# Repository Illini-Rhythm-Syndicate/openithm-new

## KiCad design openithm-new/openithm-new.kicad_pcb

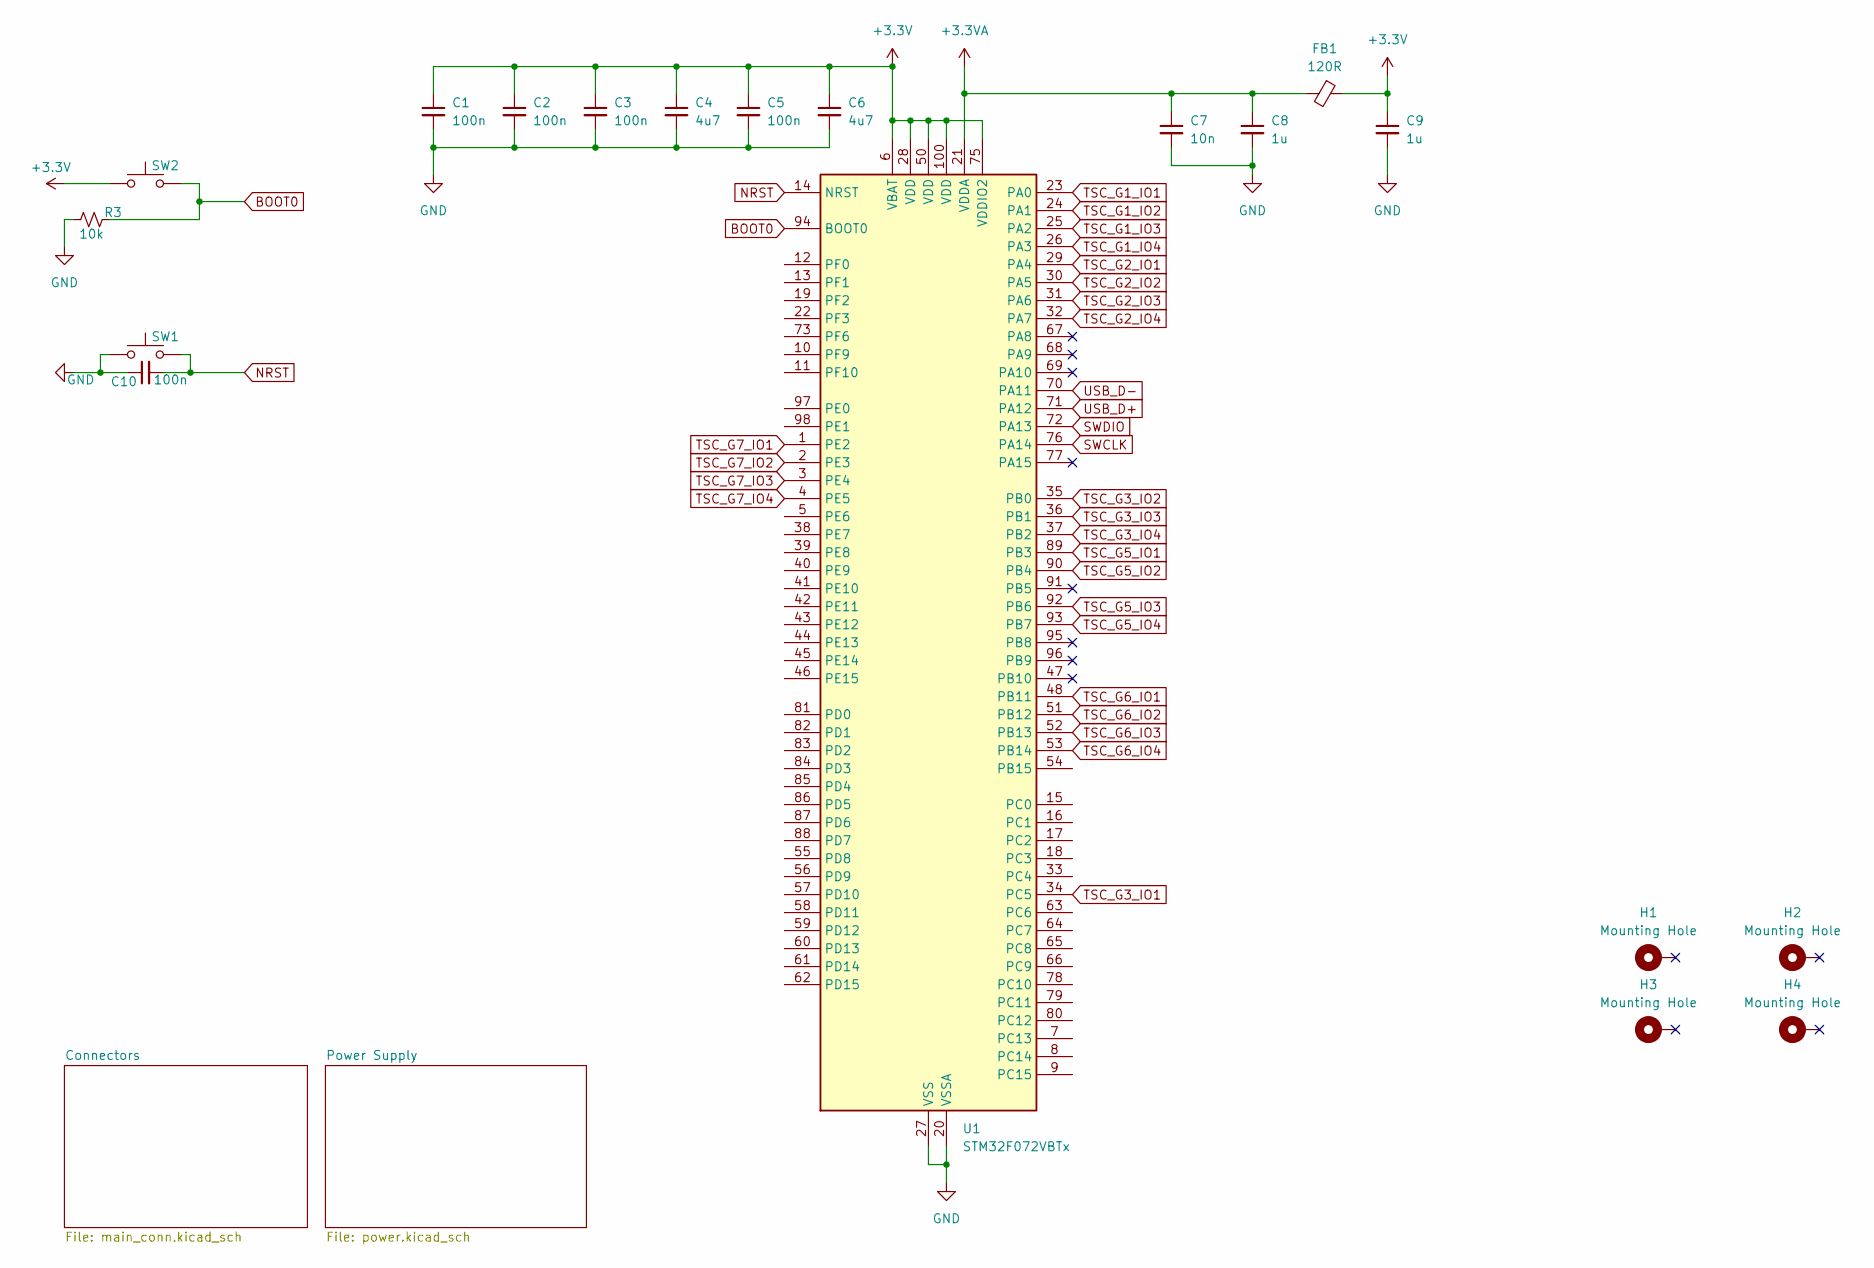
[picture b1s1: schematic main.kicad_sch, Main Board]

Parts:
C1, C2, C3, C5, C10: 100n; C_0402_1005Metric
C4, C6: 4u7; C_0603_1608Metric
C7: 10n; C_0402_1005Metric
C8, C9: 1u; C_0603_1608Metric
FB1: 120R; L_0603_1608Metric
H1, H2, H3, H4: Mounting Hole; MountingHole_2.2mm_M2_Pad
R3: 10k; R_0402_1005Metric
SW1, SW2: SW_Push; SW_Tactile_SPST_NO_Straight_CK_PTS636Sx25SMTRLFS
U1: STM32F072VBTx; LQFP-100_14x14mm_P0.5mm

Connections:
+3.3V: C1.1, C2.1, C3.1, C4.1, C5.1, C6.1, C9.1, FB1.1, SW2.1, U1.6 (VBAT), U1.28 (VDD), U1.50 (VDD), U1.75 (VDDIO2), U1.100 (VDD); also elsewhere on the board
+3.3VA: C7.1, C8.1, FB1.2, U1.21 (VDDA)
BOOT0: R3.2, SW2.2, U1.94 (BOOT0)
GND: C1.2, C2.2, C3.2, C4.2, C5.2, C6.2, C7.2, C8.2, C9.2, C10.1, R3.1, SW1.1, U1.20 (VSSA), U1.27 (VSS), U1.49 (VSS), U1.74 (VSS), U1.99 (VSS); also elsewhere on the board
NRST: C10.2, SW1.2, U1.14 (NRST)
SWCLK: U1.76 (PA14); also elsewhere on the board
SWDIO: U1.72 (PA13); also elsewhere on the board
TSC_G1_IO1: U1.23 (PA0); also elsewhere on the board
TSC_G1_IO2: U1.24 (PA1); also elsewhere on the board
TSC_G1_IO3: U1.25 (PA2); also elsewhere on the board
TSC_G1_IO4: U1.26 (PA3); also elsewhere on the board
TSC_G2_IO1: U1.29 (PA4); also elsewhere on the board
TSC_G2_IO2: U1.30 (PA5); also elsewhere on the board
TSC_G2_IO3: U1.31 (PA6); also elsewhere on the board
TSC_G2_IO4: U1.32 (PA7); also elsewhere on the board
TSC_G3_IO1: U1.34 (PC5); also elsewhere on the board
TSC_G3_IO2: U1.35 (PB0); also elsewhere on the board
TSC_G3_IO3: U1.36 (PB1); also elsewhere on the board
TSC_G3_IO4: U1.37 (PB2); also elsewhere on the board
TSC_G5_IO1: U1.89 (PB3); also elsewhere on the board
TSC_G5_IO2: U1.90 (PB4); also elsewhere on the board
TSC_G5_IO3: U1.92 (PB6); also elsewhere on the board
TSC_G5_IO4: U1.93 (PB7)
TSC_G6_IO1: U1.48 (PB11); also elsewhere on the board
TSC_G6_IO2: U1.51 (PB12); also elsewhere on the board
TSC_G6_IO3: U1.52 (PB13); also elsewhere on the board
TSC_G6_IO4: U1.53 (PB14)
TSC_G7_IO1: U1.1 (PE2); also elsewhere on the board
TSC_G7_IO2: U1.2 (PE3); also elsewhere on the board
TSC_G7_IO3: U1.3 (PE4); also elsewhere on the board
TSC_G7_IO4: U1.4 (PE5); also elsewhere on the board
USB_D+: U1.71 (PA12); also elsewhere on the board
USB_D-: U1.70 (PA11); also elsewhere on the board

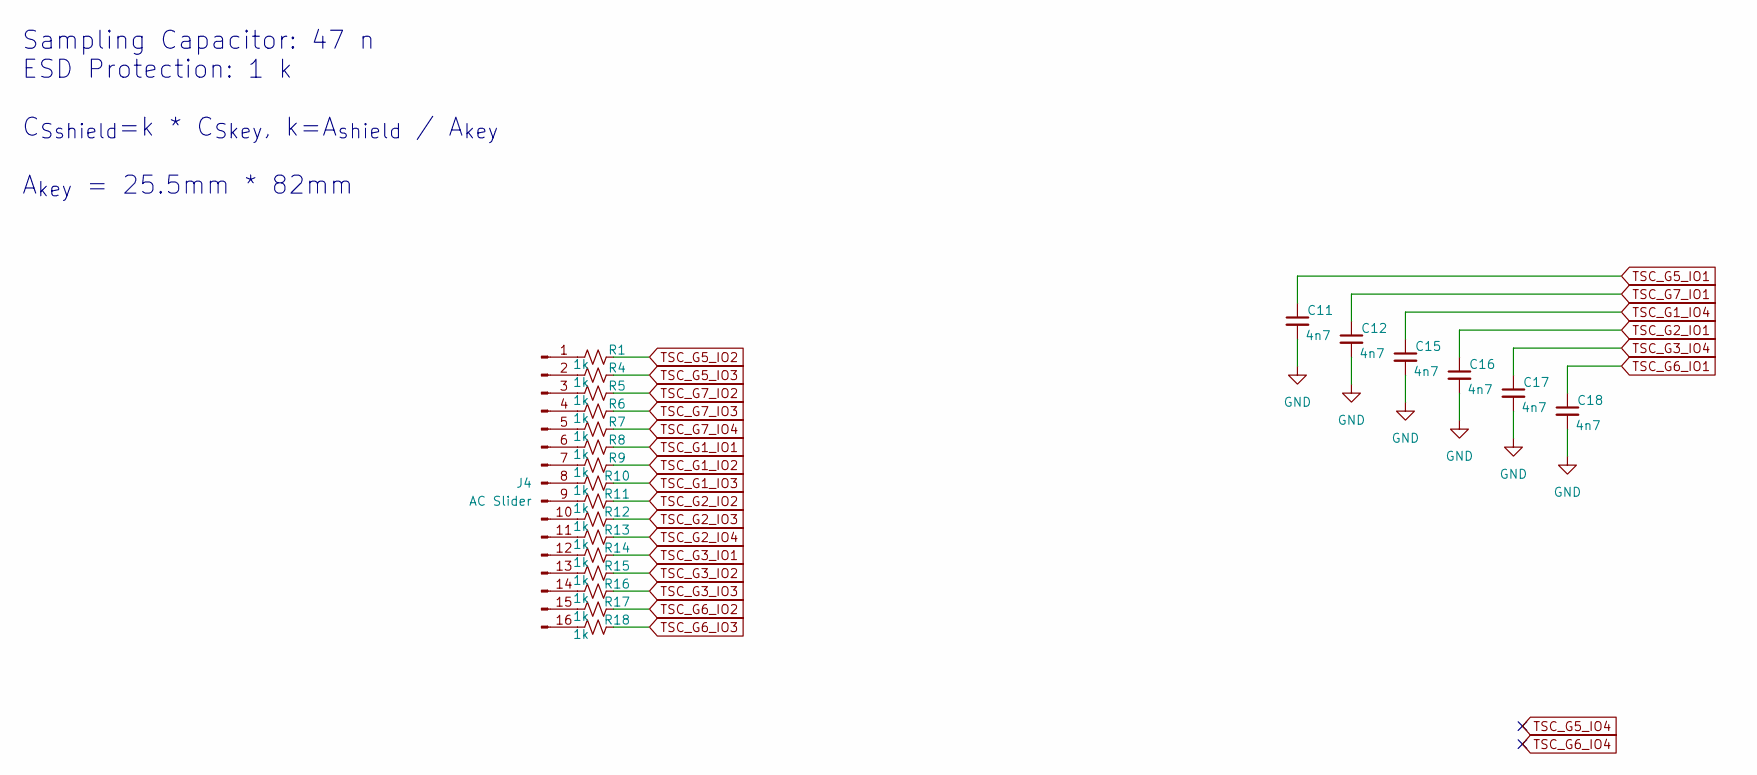
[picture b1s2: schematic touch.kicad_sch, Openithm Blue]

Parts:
C11, C12, C15, C16, C17, C18: 4n7; C_0402_1005Metric
J4: AC Slider; AC_SLIDER
R1, R4, R5, R6, R7, R8, R9, R10, R11, R12, R13, R14, R15, R16, R17, R18: 1k; R_0402_1005Metric

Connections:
GND: C11.2, C12.2, C15.2, C16.2, C17.2, C18.2; also elsewhere on the board
unnamed: J4.1, R1.1
unnamed: J4.2, R4.1
unnamed: J4.3, R5.1
unnamed: J4.4, R6.1
unnamed: J4.5, R7.1
unnamed: J4.6, R8.1
unnamed: J4.7, R9.1
unnamed: J4.8, R10.1
unnamed: J4.9, R11.1
unnamed: J4.10, R12.1
unnamed: J4.11, R13.1
unnamed: J4.12, R14.1
unnamed: J4.13, R15.1
unnamed: J4.14, R16.1
unnamed: J4.15, R17.1
unnamed: J4.16, R18.1
TSC_G1_IO1: R8.2; also elsewhere on the board
TSC_G1_IO2: R9.2; also elsewhere on the board
TSC_G1_IO3: R10.2; also elsewhere on the board
TSC_G1_IO4: C15.1; also elsewhere on the board
TSC_G2_IO1: C16.1; also elsewhere on the board
TSC_G2_IO2: R11.2; also elsewhere on the board
TSC_G2_IO3: R12.2; also elsewhere on the board
TSC_G2_IO4: R13.2; also elsewhere on the board
TSC_G3_IO1: R14.2; also elsewhere on the board
TSC_G3_IO2: R15.2; also elsewhere on the board
TSC_G3_IO3: R16.2; also elsewhere on the board
TSC_G3_IO4: C17.1; also elsewhere on the board
TSC_G5_IO1: C11.1; also elsewhere on the board
TSC_G5_IO2: R1.2; also elsewhere on the board
TSC_G5_IO3: R4.2; also elsewhere on the board
TSC_G6_IO1: C18.1; also elsewhere on the board
TSC_G6_IO2: R17.2; also elsewhere on the board
TSC_G6_IO3: R18.2; also elsewhere on the board
TSC_G7_IO1: C12.1; also elsewhere on the board
TSC_G7_IO2: R5.2; also elsewhere on the board
TSC_G7_IO3: R6.2; also elsewhere on the board
TSC_G7_IO4: R7.2; also elsewhere on the board

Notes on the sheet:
Sampling Capacitor: 47 n ESD Protection: 1 k C_{Sshield}=k * C_{Skey}, k=A_{shield} / A_{key} A_{key} = 25.5mm * 82mm

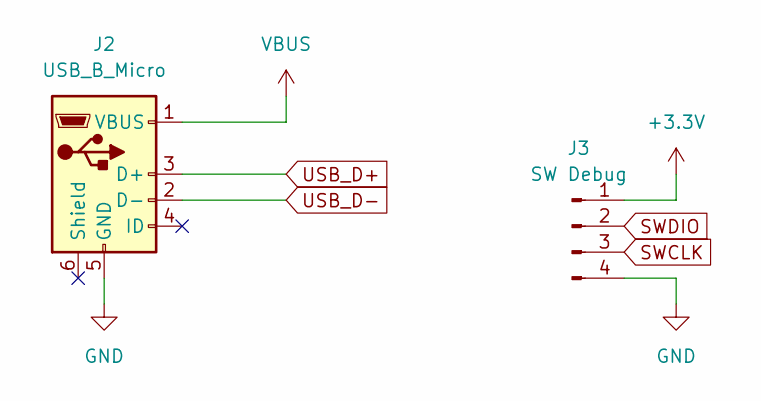
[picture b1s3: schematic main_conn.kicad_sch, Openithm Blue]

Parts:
J2: USB_B_Micro; USB_Micro-B_Wuerth_629105150521
J3: SW Debug; PinHeader_1x04_P2.54mm_Horizontal

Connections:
+3.3V: J3.1; also elsewhere on the board
GND: J2.5 (GND), J3.4; also elsewhere on the board
SWCLK: J3.3; also elsewhere on the board
SWDIO: J3.2; also elsewhere on the board
USB_D+: J2.3 (D+); also elsewhere on the board
USB_D-: J2.2 (D-); also elsewhere on the board
VBUS: J2.1 (VBUS); also elsewhere on the board

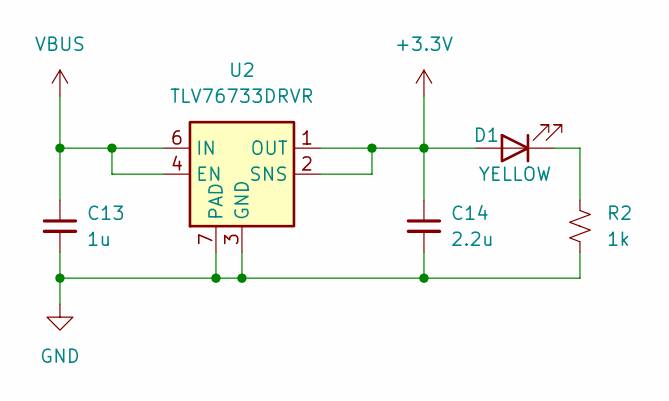
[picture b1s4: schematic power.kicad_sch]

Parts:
C13: 1u; C_0603_1608Metric
C14: 2.2u; C_0603_1608Metric
D1: YELLOW; LED_0603_1608Metric
R2: 1k; R_0402_1005Metric
U2: TLV76733DRVR; WSON-6-1EP_2x2mm_P0.65mm_EP1x1.6mm

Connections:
+3.3V: C14.1, D1.2 (A), U2.1 (OUT), U2.2 (SNS); also elsewhere on the board
GND: C13.2, C14.2, R2.2, U2.3 (GND), U2.5 (GND), U2.7 (PAD); also elsewhere on the board
unnamed: D1.1 (K), R2.1
VBUS: C13.1, U2.4 (EN), U2.6 (IN); also elsewhere on the board

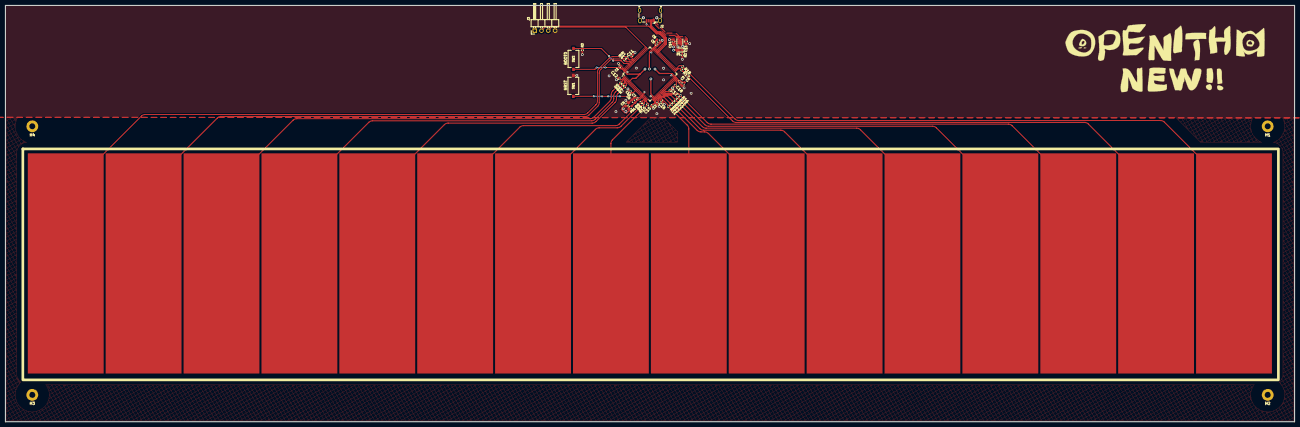
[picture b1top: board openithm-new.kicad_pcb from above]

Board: 2 copper layers, 480.0 x 155.0 mm, 49 parts (0 on the bottom side), 49 nets.

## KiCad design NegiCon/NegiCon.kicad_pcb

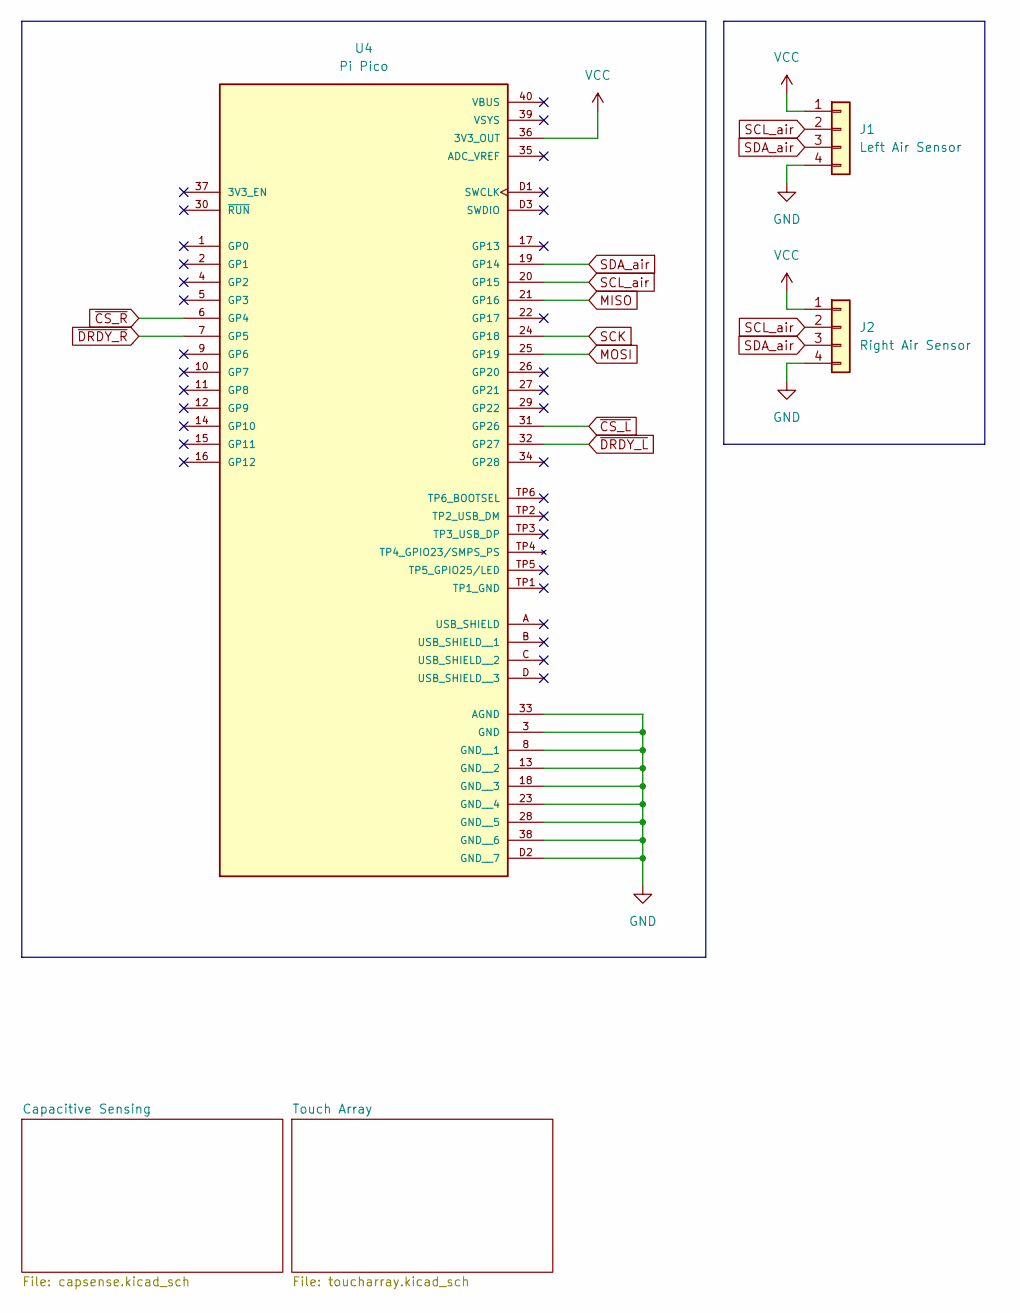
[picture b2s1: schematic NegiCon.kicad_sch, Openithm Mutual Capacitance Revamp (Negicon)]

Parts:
J1: Left Air Sensor; Molex_Nano-Fit_105313-xx04_1x04_P2.50mm_Horizontal
J2: Right Air Sensor; Molex_Nano-Fit_105313-xx04_1x04_P2.50mm_Horizontal
U4: Pi Pico; MODULE_SC0915; PARTREV 1.9

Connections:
GND: J1.4, J2.4, U4.3 (GND), U4.8 (GND__1), U4.13 (GND__2), U4.18 (GND__3), U4.23 (GND__4), U4.28 (GND__5), U4.33 (AGND), U4.38 (GND__6), U4.D2 (GND__7); also elsewhere on the board
MISO: U4.21 (GP16); also elsewhere on the board
MOSI: U4.25 (GP19); also elsewhere on the board
SCK: U4.24 (GP18); also elsewhere on the board
SCL_air: J1.2, J2.2, U4.20 (GP15)
SDA_air: J1.3, J2.3, U4.19 (GP14)
VCC: J1.1, J2.1, U4.36 (3V3_OUT); also elsewhere on the board
~CS_L: U4.31 (GP26); also elsewhere on the board
~CS_R: U4.6 (GP4); also elsewhere on the board
~DRDY_L: U4.32 (GP27); also elsewhere on the board
~DRDY_R: U4.7 (GP5); also elsewhere on the board

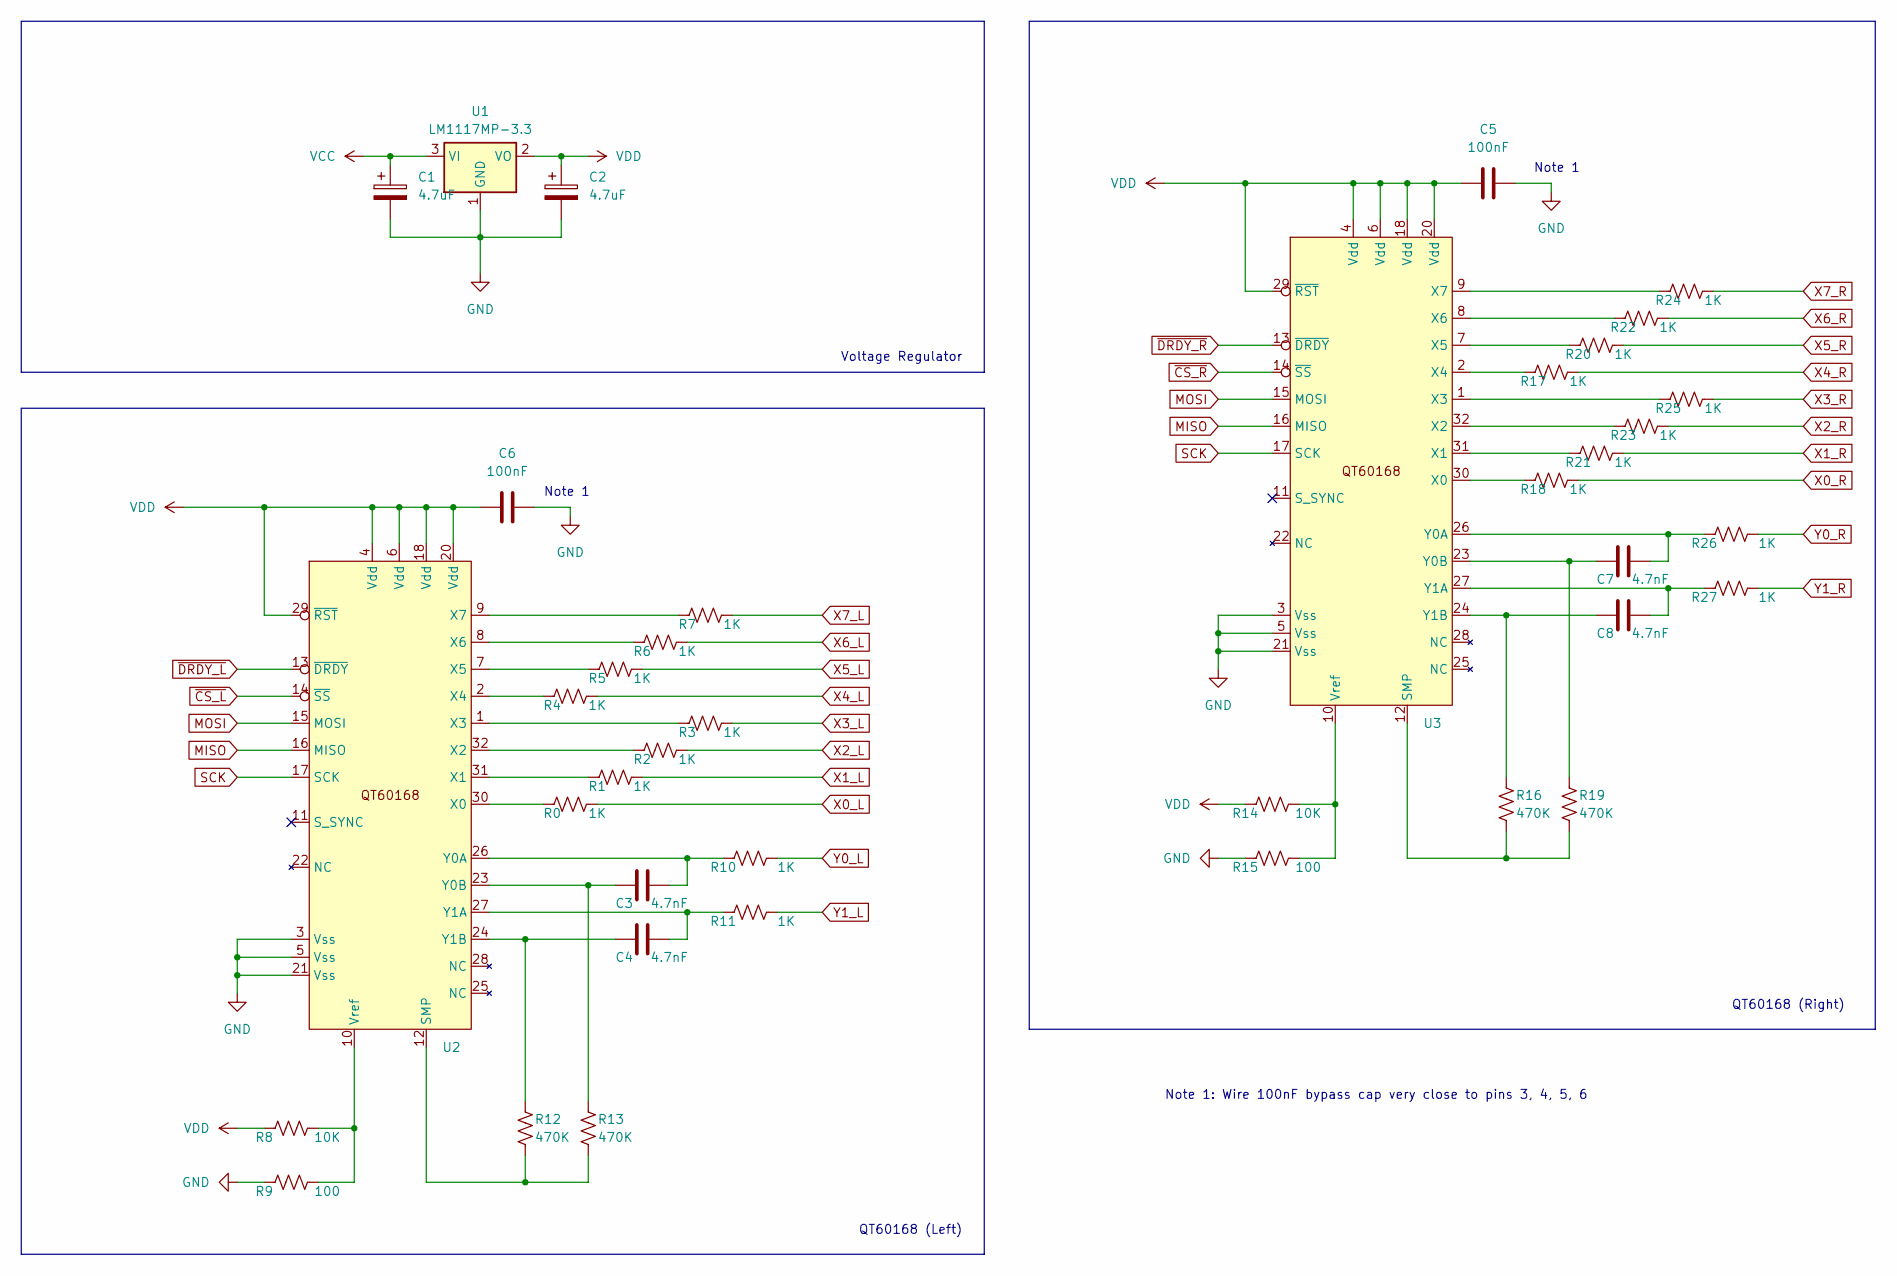
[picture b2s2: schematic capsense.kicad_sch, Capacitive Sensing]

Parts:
C1, C2: 4.7uF; C_0603_1608Metric
C3, C4, C7, C8: 4.7nF; C_0603_1608Metric
C5, C6: 100nF; C_0603_1608Metric
R0, R1, R2, R3, R4, R5, R6, R7, R10, R11, R17, R18, R20, R21, R22, R23, R24, R25, R26, R27: 1K; R_0603_1608Metric
R8, R14: 10K; R_0603_1608Metric
R9, R15: 100; R_0603_1608Metric
R12, R13, R16, R19: 470K; R_0603_1608Metric
U1: LM1117MP-3.3; SOT-223-3_TabPin2
U2, U3: TQFP-32_7x7mm_P0.8mm

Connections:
GND: C1.2, C2.2, C5.2, C6.2, R9.1, R15.1, U1.1 (GND), U2.3 (Vss), U2.5 (Vss), U2.21 (Vss), U3.3 (Vss), U3.5 (Vss), U3.21 (Vss); also elsewhere on the board
MISO: U2.16 (MISO), U3.16 (MISO); also elsewhere on the board
MOSI: U2.15 (MOSI), U3.15 (MOSI); also elsewhere on the board
unnamed: R12.2, R13.2, U2.12 (SMP)
unnamed: R8.1, R9.2, U2.10 (Vref)
unnamed: R0.1, U2.30 (X0)
unnamed: R1.1, U2.31 (X1)
unnamed: R2.1, U2.32 (X2)
unnamed: R3.1, U2.1 (X3)
unnamed: R4.1, U2.2 (X4)
unnamed: R5.1, U2.7 (X5)
unnamed: R6.1, U2.8 (X6)
unnamed: R7.1, U2.9 (X7)
unnamed: C3.2, R10.1, U2.26 (Y0A)
unnamed: C3.1, R13.1, U2.23 (Y0B)
unnamed: C4.2, R11.1, U2.27 (Y1A)
unnamed: C4.1, R12.1, U2.24 (Y1B)
unnamed: R16.2, R19.2, U3.12 (SMP)
unnamed: R14.1, R15.2, U3.10 (Vref)
unnamed: R18.1, U3.30 (X0)
unnamed: R21.1, U3.31 (X1)
unnamed: R23.1, U3.32 (X2)
unnamed: R25.1, U3.1 (X3)
unnamed: R17.1, U3.2 (X4)
unnamed: R20.1, U3.7 (X5)
unnamed: R22.1, U3.8 (X6)
unnamed: R24.1, U3.9 (X7)
unnamed: C7.2, R26.1, U3.26 (Y0A)
unnamed: C7.1, R19.1, U3.23 (Y0B)
unnamed: C8.2, R27.1, U3.27 (Y1A)
unnamed: C8.1, R16.1, U3.24 (Y1B)
SCK: U2.17 (SCK), U3.17 (SCK); also elsewhere on the board
VCC: C1.1, U1.3 (VI); also elsewhere on the board
VDD: C2.1, C5.1, C6.1, R8.2, R14.2, U1.2 (VO), U2.4 (Vdd), U2.6 (Vdd), U2.18 (Vdd), U2.20 (Vdd), U2.29 (~RST), U3.4 (Vdd), U3.6 (Vdd), U3.18 (Vdd), U3.20 (Vdd), U3.29 (~RST)
X0_L: R0.2; also elsewhere on the board
X0_R: R18.2; also elsewhere on the board
X1_L: R1.2; also elsewhere on the board
X1_R: R21.2; also elsewhere on the board
X2_L: R2.2; also elsewhere on the board
X2_R: R23.2; also elsewhere on the board
X3_L: R3.2; also elsewhere on the board
X3_R: R25.2; also elsewhere on the board
X4_L: R4.2; also elsewhere on the board
X4_R: R17.2; also elsewhere on the board
X5_L: R5.2; also elsewhere on the board
X5_R: R20.2; also elsewhere on the board
X6_L: R6.2; also elsewhere on the board
X6_R: R22.2; also elsewhere on the board
X7_L: R7.2; also elsewhere on the board
X7_R: R24.2; also elsewhere on the board
Y0_L: R10.2; also elsewhere on the board
Y0_R: R26.2; also elsewhere on the board
Y1_L: R11.2; also elsewhere on the board
Y1_R: R27.2; also elsewhere on the board
~CS_L: U2.14 (~SS); also elsewhere on the board
~CS_R: U3.14 (~SS); also elsewhere on the board
~DRDY_L: U2.13 (~DRDY); also elsewhere on the board
~DRDY_R: U3.13 (~DRDY); also elsewhere on the board

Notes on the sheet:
QT60168 (Right)
Voltage Regulator
QT60168 (Left)
Note 1
Note 1: Wire 100nF bypass cap very close to pins 3, 4, 5, 6

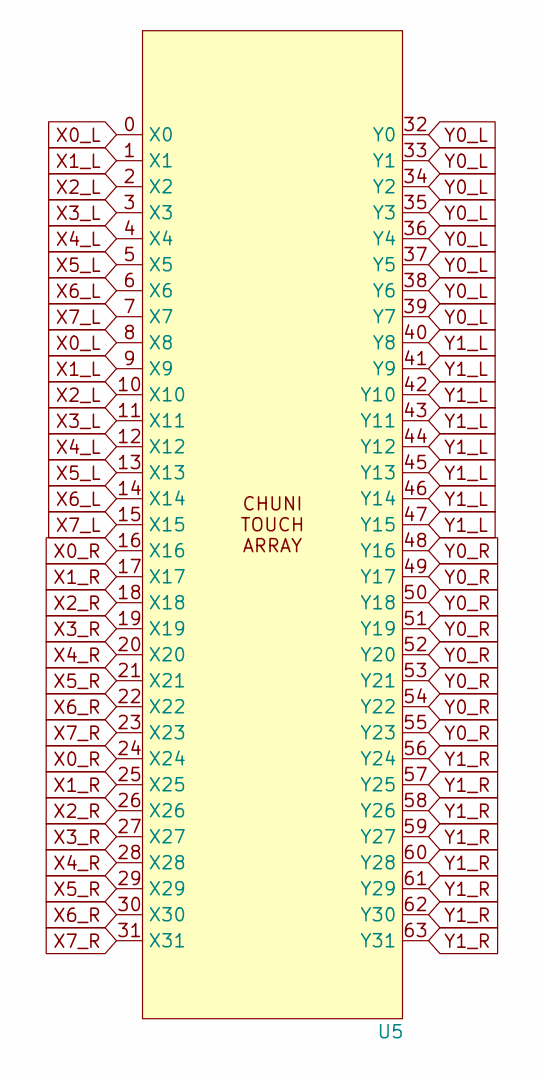
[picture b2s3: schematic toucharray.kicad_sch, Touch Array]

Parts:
U5: CH3MM64

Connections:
X0_L: U5.0 (X0), U5.8 (X8); also elsewhere on the board
X0_R: U5.16 (X16), U5.24 (X24); also elsewhere on the board
X1_L: U5.1 (X1), U5.9 (X9); also elsewhere on the board
X1_R: U5.17 (X17), U5.25 (X25); also elsewhere on the board
X2_L: U5.2 (X2), U5.10 (X10); also elsewhere on the board
X2_R: U5.18 (X18), U5.26 (X26); also elsewhere on the board
X3_L: U5.3 (X3), U5.11 (X11); also elsewhere on the board
X3_R: U5.19 (X19), U5.27 (X27); also elsewhere on the board
X4_L: U5.4 (X4), U5.12 (X12); also elsewhere on the board
X4_R: U5.20 (X20), U5.28 (X28); also elsewhere on the board
X5_L: U5.5 (X5), U5.13 (X13); also elsewhere on the board
X5_R: U5.21 (X21), U5.29 (X29); also elsewhere on the board
X6_L: U5.6 (X6), U5.14 (X14); also elsewhere on the board
X6_R: U5.22 (X22), U5.30 (X30); also elsewhere on the board
X7_L: U5.7 (X7), U5.15 (X15); also elsewhere on the board
X7_R: U5.23 (X23), U5.31 (X31); also elsewhere on the board
Y0_L: U5.32 (Y0), U5.33 (Y1), U5.34 (Y2), U5.35 (Y3), U5.36 (Y4), U5.37 (Y5), U5.38 (Y6), U5.39 (Y7); also elsewhere on the board
Y0_R: U5.48 (Y16), U5.49 (Y17), U5.50 (Y18), U5.51 (Y19), U5.52 (Y20), U5.53 (Y21), U5.54 (Y22), U5.55 (Y23); also elsewhere on the board
Y1_L: U5.40 (Y8), U5.41 (Y9), U5.42 (Y10), U5.43 (Y11), U5.44 (Y12), U5.45 (Y13), U5.46 (Y14), U5.47 (Y15); also elsewhere on the board
Y1_R: U5.56 (Y24), U5.57 (Y25), U5.58 (Y26), U5.59 (Y27), U5.60 (Y28), U5.61 (Y29), U5.62 (Y30), U5.63 (Y31); also elsewhere on the board

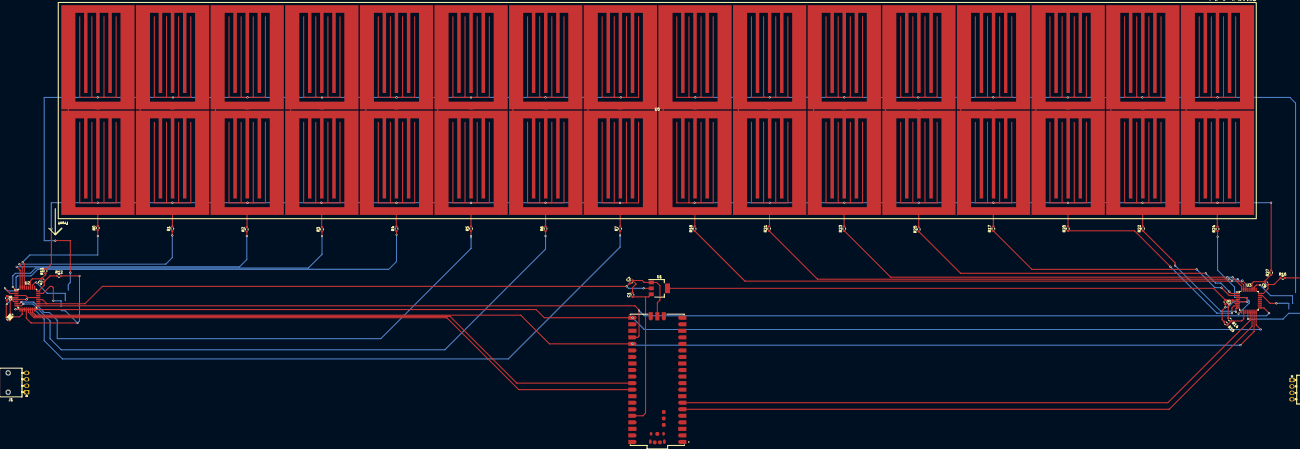
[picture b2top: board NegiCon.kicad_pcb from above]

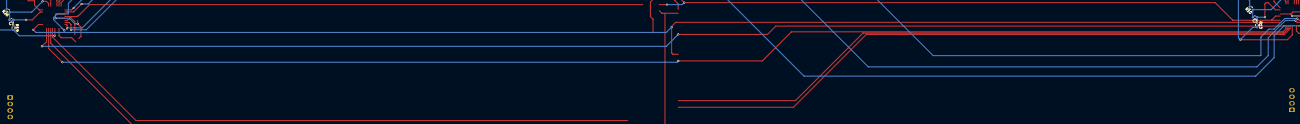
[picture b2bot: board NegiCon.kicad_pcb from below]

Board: 2 copper layers, 43 parts (6 on the bottom side), 60 nets.

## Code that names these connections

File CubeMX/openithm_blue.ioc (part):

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Mcu.Name=STM32F072V(8-B)Tx
Mcu.Package=LQFP100
Mcu.UserName=STM32F072VBTx
PA0.Mode=G1_IO1-Sampling
PA0.Signal=TSC_G1_IO1
PA1.Mode=G1_IO2-Channel
PA1.Signal=TSC_G1_IO2
PA11.Mode=Device
PA11.Signal=USB_DM
PA12.Mode=Device
PA12.Signal=USB_DP
PA13.Mode=Serial_Wire
PA13.Signal=SYS_SWDIO
PA14.Mode=Serial_Wire
PA14.Signal=SYS_SWCLK
PA2.Mode=G1_IO3-Channel
PA2.Signal=TSC_G1_IO3
PA3.Mode=G1_IO4-Channel
PA3.Signal=TSC_G1_IO4
PA4.Mode=G2_IO1-Sampling
PA4.Signal=TSC_G2_IO1
PA5.Mode=G2_IO2-Channel
PA5.Signal=TSC_G2_IO2
PA6.Mode=G2_IO3-Channel
PA6.Signal=TSC_G2_IO3
PA7.Mode=G2_IO4-Channel
PA7.Signal=TSC_G2_IO4
PB0.Mode=G3_IO2-Channel
PB0.Signal=TSC_G3_IO2
PB1.Mode=G3_IO3-Channel
PB1.Signal=TSC_G3_IO3
PB11.Mode=G6_IO1-Sampling
PB11.Signal=TSC_G6_IO1
PB12.Mode=G6_IO2-Channel
PB12.Signal=TSC_G6_IO2
PB13.Mode=G6_IO3-Channel
PB13.Signal=TSC_G6_IO3
PB14.Mode=G6_IO4-Channel
PB14.Signal=TSC_G6_IO4
PB2.Mode=G3_IO4-Channel
PB2.Signal=TSC_G3_IO4
PB3.Mode=G5_IO1-Sampling
PB3.Signal=TSC_G5_IO1
PB4.Mode=G5_IO2-Channel
PB4.Signal=TSC_G5_IO2
PB6.Mode=G5_IO3-Channel
PB6.Signal=TSC_G5_IO3
PB7.Mode=G5_IO4-Channel
PB7.Signal=TSC_G5_IO4
PB8.Mode=I2C
PB8.Signal=I2C1_SCL
PB9.Mode=I2C
PB9.Signal=I2C1_SDA
PC5.Mode=G3_IO1-Sampling
PC5.Signal=TSC_G3_IO1
PE2.Mode=G7_IO1-Sampling
PE2.Signal=TSC_G7_IO1
PE3.Mode=G7_IO2-Channel
PE3.Signal=TSC_G7_IO2
PE4.Mode=G7_IO3-Channel
PE4.Signal=TSC_G7_IO3
PE5.Mode=G7_IO4-Channel
PE5.Signal=TSC_G7_IO4
PF0-OSC_IN.Mode=HSE-External-Oscillator
PF0-OSC_IN.Signal=RCC_OSC_IN
PF1-OSC_OUT.Mode=HSE-External-Oscillator
PF1-OSC_OUT.Signal=RCC_OSC_OUT
RCC.SYSCLKFreq_VALUE=48000000
RCC.SYSCLKSource=RCC_SYSCLKSOURCE_HSI48
board=custom

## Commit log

2024-02-04 add connectors for air sensors
2024-11-30 Initial layout of Openi dev board
2024-11-30 CubeMX project generation
2024-12-24 Finished Rev.1

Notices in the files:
parts and their libraries:
©Illini Rhythm Syndicate
